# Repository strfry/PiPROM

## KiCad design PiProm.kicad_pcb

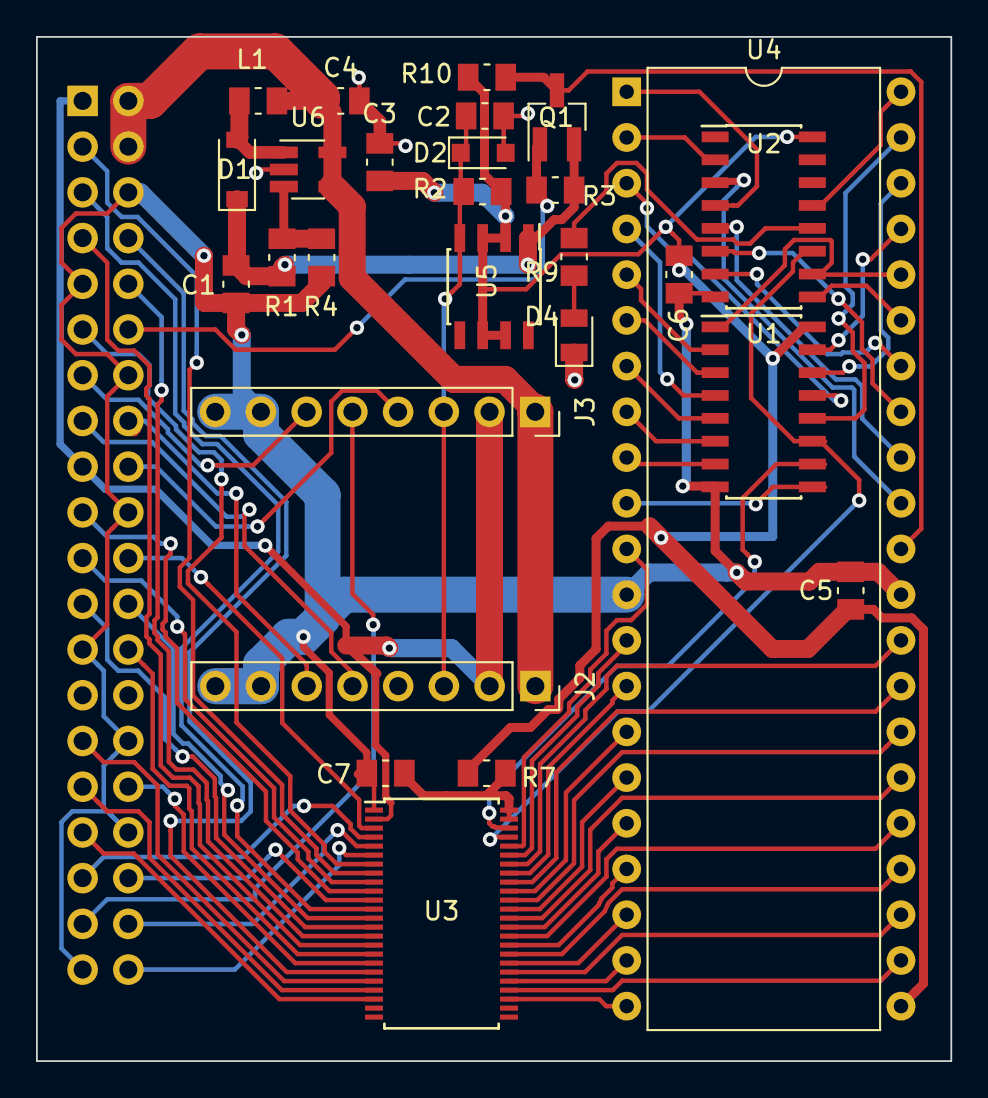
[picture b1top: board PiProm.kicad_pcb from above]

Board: 2 copper layers, 50.8 x 56.9 mm, 28 parts (1 on the bottom side), 78 nets.

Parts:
C1, C4: 1u; C_0805_2012Metric_Pad1.15x1.50mm_HandSolder
C2, C3: 10u; C_0805_2012Metric_Pad1.15x1.50mm_HandSolder
C5, C6, C7: 100n; C_0805_2012Metric_Pad1.15x1.50mm_HandSolder
D1: 1N5819; D_SOD-123
D2: 5V6; D_SOD-323_HandSoldering
D4: LED; D_0805_2012Metric_Pad0.97x1.50mm_HandSolder
J1: Raspberry_Pi_2_3; PinSocket_2x20_P2.54mm_Vertical
J2, J3: Conn_01x08_Female; PinSocket_1x08_P2.54mm_Vertical
L1: 10u; L_0805_2012Metric_Pad1.15x1.50mm_HandSolder
Q1: BSS84; SOT-23_Handsoldering
R1, R3: 15k; R_0805_2012Metric_Pad1.15x1.50mm_HandSolder
R2, R4: 1k5; R_0805_2012Metric_Pad1.15x1.50mm_HandSolder
R7: 200k; R_0805_2012Metric_Pad1.15x1.50mm_HandSolder
R9: R; R_0805_2012Metric_Pad1.15x1.50mm_HandSolder
R10: 10k; R_0805_2012Metric_Pad1.15x1.50mm_HandSolder
U1, U2: 4040; SOIC-16_3.9x9.9mm_P1.27mm
U3: GTL2000; TSSOP-48_6.1x12.5mm_P0.5mm
U4: 27C160; DIP-42_W15.24mm
U5: LM317L_SO8; SOIC-8_3.9x4.9mm_P1.27mm
U6: AP3012; SOT-23-5_HandSoldering

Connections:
+3V3: J1.1, J1.17, J2.2, J3.2, U3.2
+5V: C4.1, J1.2, J1.4, J2.1, J3.1, L1.1, U6.4, U6.5
/A0: U1.9, U4.10
/A1: U1.7, U4.9
/A2: U1.6, U4.8
/A3: U1.5, U4.7
/A4: U1.3, U4.6
/A5: U1.2, U4.5
/A6: U1.4, U4.4
/A7: U1.13, U4.3
/A8: U1.12, U4.41
/A9: U1.14, U4.40
/A10: U1.15, U4.39
/A11: U1.1, U2.10, U4.38
/A12: U2.9, U4.37
/A13: U2.7, U4.36
/A14: U2.6, U4.35
/A15: U2.5, U4.34
/A16: U2.3, U4.33
/A17: U2.2, U4.2
/A18: U2.4, U4.1
/A19: U2.13, U4.42
/ADDR_CLK: U1.10, U3.46
/ADDR_RST: U1.11, U2.11, U3.45
/BUTTON1: J1.15, J2.5
/BUTTON2: J1.16, J2.6
/BUTTON3: J1.37, J3.5
/BUTTON4: J1.13, J3.6
/CE: U3.44, U4.11
/D0: U3.41, U4.14
/D1: U3.37, U4.16
/D2: U3.33, U4.18
/D3: U3.29, U4.20
/D4: U3.28, U4.23
/D5: U3.32, U4.25
/D6: U3.36, U4.27
/D7: U3.40, U4.29
/D8: U3.39, U4.15
/D9: U3.35, U4.17
/D10: U3.31, U4.19
/D11: U3.27, U4.21
/D12: U3.30, U4.24
/D13: U3.34, U4.26
/D14: U3.38, U4.28
/D15: U3.42, U4.30
/GPIO2: J1.3, U3.8
/GPIO3: J1.5, U3.12
/GPIO4: J1.7, U3.16
/GPIO5: J1.29, U3.20
/GPIO6: J1.31, U3.21
/GPIO7: J1.26, U3.17
/GPIO8: J1.24, U3.13
/GPIO9: J1.21, U3.9
/GPIO10: J1.19, U3.10
/GPIO11: J1.23, U3.14
/GPIO12: J1.32, U3.18
/GPIO13: J1.33, U3.22
/GPIO14: J1.8, U3.19
/GPIO15: J1.10, U3.15
/GPIO16: J1.36, U3.11
/GPIO17: J1.11, U3.7
/GPIO19: J1.35, U3.4
/GPIO20: J1.38, U3.5
/GPIO21: J1.40, U3.6
/GPIO25: J1.22, U3.3
/LED_enable: J1.18, J3.4
/OE: U3.43, U4.13
/VCC_ADJ: C2.1, D2.1, J2.3, J3.3, R2.2, U5.4
/Vpp_enable: J1.12, Q1.1, R3.2
GND: C1.2, C2.2, C3.2, C4.2, C5.2, C6.2, C7.2, D2.2, D4.1, J1.6, J1.9, J1.14, J1.20, J1.25, J1.30, J1.34, J1.39, J2.7, J2.8, J3.7, J3.8, R4.2, U1.8, U2.8, U3.1, U4.12, U4.31, U6.2
unnamed: C1.1, D1.1, Q1.2, R1.1, R3.1, U5.1
unnamed: C7.1, R7.2, U3.47, U3.48
unnamed: D1.2, L1.2, U6.1
unnamed: D4.2, R9.2
unnamed: R1.2, R4.1, U6.3
unnamed: R9.1, U2.12
VCC: C3.1, C5.1, C6.1, R2.1, R7.1, R10.2, U1.16, U2.16, U4.22, U5.2, U5.3, U5.6, U5.7
VPP: Q1.3, R10.1, U4.32

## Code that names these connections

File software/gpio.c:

//
//  How to access GPIO registers from C-code on the Raspberry-Pi
//  Example program
//  15-January-2012
//  Dom and Gert
//  Revised: 15-Feb-2013
 
 
// Access from ARM Running Linux
 
//#define BCM2708_PERI_BASE        0x20000000

// for raspi 3:
#define BCM2708_PERI_BASE        0x3F000000
#define GPIO_BASE                (BCM2708_PERI_BASE + 0x200000) /* GPIO controller */

#include "img_1.h" 
 
#include <stdio.h>
#include <stdlib.h>
#include <fcntl.h>
#include <sys/mman.h>
#include <sys/time.h>
#include <unistd.h>
 
#define PAGE_SIZE (4*1024)
#define BLOCK_SIZE (4*1024)
 
int  mem_fd;
void *gpio_map;
 
// I/O access
volatile unsigned *gpio;
 
 
// GPIO setup macros. Always use INP_GPIO(x) before using OUT_GPIO(x) or SET_GPIO_ALT(x,y)
#define INP_GPIO(g) *(gpio+((g)/10)) &= ~(7<<(((g)%10)*3))
#define OUT_GPIO(g) *(gpio+((g)/10)) |=  (1<<(((g)%10)*3))
#define SET_GPIO_ALT(g,a) *(gpio+(((g)/10))) |= (((a)<=3?(a)+4:(a)==4?3:2)<<(((g)%10)*3))
 
#define GPIO_SET *(gpio+7)  // sets   bits which are 1 ignores bits which are 0
#define GPIO_CLR *(gpio+10) // clears bits which are 1 ignores bits which are 0
 
#define GET_GPIO(g) (*(gpio+13)&(1<<g)) // 0 if LOW, (1<<g) if HIGH
 
#define GPIO_PULL *(gpio+37) // Pull up/pull down
#define GPIO_PULLCLK0 *(gpio+38) // Pull up/pull down clock


#define DATA_BASE 2
#define CHIP_ENABLEN 20
#define OUTPUT_ENABLEN 21
#define ADDR_CLK 25
#define ADDR_RST 19
#define VPP_ENABLE 18
#define LED_ENABLE 24



long long getusecs() {
    struct timeval tv;
    gettimeofday(&tv, 0);

    return tv.tv_sec * 1000000 + tv.tv_usec;
}

void wait_usec(int usecs) {
    long long start = getusecs();
    while (getusecs() < (start + usecs)) {
    }
}


int get_data() {
	return ((*(gpio+13) >> DATA_BASE) & (0xffff));
}
 
void setup_io();

int main(int argc, char **argv)
{
  int g,rep;

  // Set up gpi pointer for direct register access
  setup_io();
 
  // Set data GPIO pins 2-18 to input
  for (int g=0; g<16; g++)
  {
	INP_GPIO(DATA_BASE + g);
//    OUT_GPIO(g);
  }

  INP_GPIO(ADDR_RST);
  INP_GPIO(ADDR_CLK);
  INP_GPIO(CHIP_ENABLEN);
  INP_GPIO(OUTPUT_ENABLEN);

  OUT_GPIO(ADDR_RST);
  OUT_GPIO(ADDR_CLK);
  OUT_GPIO(CHIP_ENABLEN);
  OUT_GPIO(OUTPUT_ENABLEN);

  puts("resetting counters");
  GPIO_SET = 1 << ADDR_RST;
  GPIO_CLR = 1 << ADDR_RST;

  GPIO_SET = 1 << ADDR_CLK;


  // enable chip
  GPIO_CLR = 1 << CHIP_ENABLEN;
  // enable output
  GPIO_CLR = 1 << OUTPUT_ENABLEN;


  if (argc >= 2) {
    if (strcmp(argv[1], "write") == 0) {
      write_image();
    } else {
      read_image();
    }
  }
 
}

void write_image() {
  for (int g=0; g<16; g++)
  {
    INP_GPIO(DATA_BASE + g);
    OUT_GPIO(g);
  }

  // enable VPP_enable
  INP_GPIO(VPP_ENABLE);
  OUT_GPIO(VPP_ENABLE);

  GPIO_SET = 1 << VPP_ENABLE;

  // disable chip
  GPIO_SET = 1 << CHIP_ENABLEN;

  // set input mode
  GPIO_SET = 1 << OUTPUT_ENABLEN;

  int i;
  for (i = 0; i < 1024 * 1024; i++) {
    unsigned short *p = gimp_image.pixel_data;

    GPIO_CLR = 0xffff << DATA_BASE;
    GPIO_SET = p[i] << DATA_BASE;
//    GPIO_SET = 0x0000 << DATA_BASE;


    // chip enable strobe
    GPIO_CLR = 1 << CHIP_ENABLEN;
    wait_usec(50);
    GPIO_SET = 1 << CHIP_ENABLEN;

    // Addr CLK
    GPIO_CLR = 1 << ADDR_CLK;
    GPIO_SET = 1 << ADDR_CLK;
  }

  GPIO_CLR = 1 << VPP_ENABLE;

}

void read_image() {
  int fb_fd = open("/dev/fb0", O_WRONLY);

  int pad = 1280 - 1024;
  int buf[1024];
  memset(buf, 0, 1024);

  int line, px = 0;

  for (line = 0; line < 1024; line++) {
    printf("address = %x, current data %x\n", line, get_data());
    write(fb_fd, buf, pad);
      for (px = 0; px < 1024; px++) {
        int data = get_data();
	write(fb_fd, &data, 2);

	GPIO_CLR = 1 << ADDR_CLK;
	GPIO_SET = 1 << ADDR_CLK;
//    wait_usec(10);

    }

    write(fb_fd, buf, pad);
  }

  return; 
}


//
// Set up a memory regions to access GPIO
//
void setup_io()
{
   /* open /dev/mem */
   if ((mem_fd = open("/dev/mem", O_RDWR|O_SYNC) ) < 0) {
      printf("can't open /dev/mem \n");
      exit(-1);
   }
 
   /* mmap GPIO */
   gpio_map = mmap(
      NULL,             //Any adddress in our space will do
      BLOCK_SIZE,       //Map length
      PROT_READ|PROT_WRITE,// Enable reading & writting to mapped memory
      MAP_SHARED,       //Shared with other processes
      mem_fd,           //File to map
      GPIO_BASE         //Offset to GPIO peripheral
   );
 
   close(mem_fd); //No need to keep mem_fd open after mmap
 
   if (gpio_map == MAP_FAILED) {
      printf("mmap error %d\n", (int)gpio_map);//errno also set!
      exit(-1);
   }
 
   // Always use volatile pointer!
   gpio = (volatile unsigned *)gpio_map; 
} // setup_io

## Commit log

2017-10-08 Added KiCAD symbol for 27C160
2017-10-08 KiCAD symbol for GTL2000
2018-01-02 v1 before annotation
2018-01-03 PCB routed v1
2018-01-03 added BOM
2018-01-05 added sym-lib-table
2018-01-06 Changed Step-Up Coil to Murata LQH32CN Re-arrange silkscreen labels
2018-01-08 Nice ground plane for switching regulator, thicker connections
2018-01-08 Added optional bypass capacitor for LM317 Adj pin, to compensate for potentially long line to potentiometer
2018-01-16 New design: - Schematic in one file - Added boost driver for UV LED
2018-01-25 - Moved LED driver to second stage board - Fixed direction of Pi GPIO connector
2018-03-17 simple read/write software
2018-06-23 added new write image
